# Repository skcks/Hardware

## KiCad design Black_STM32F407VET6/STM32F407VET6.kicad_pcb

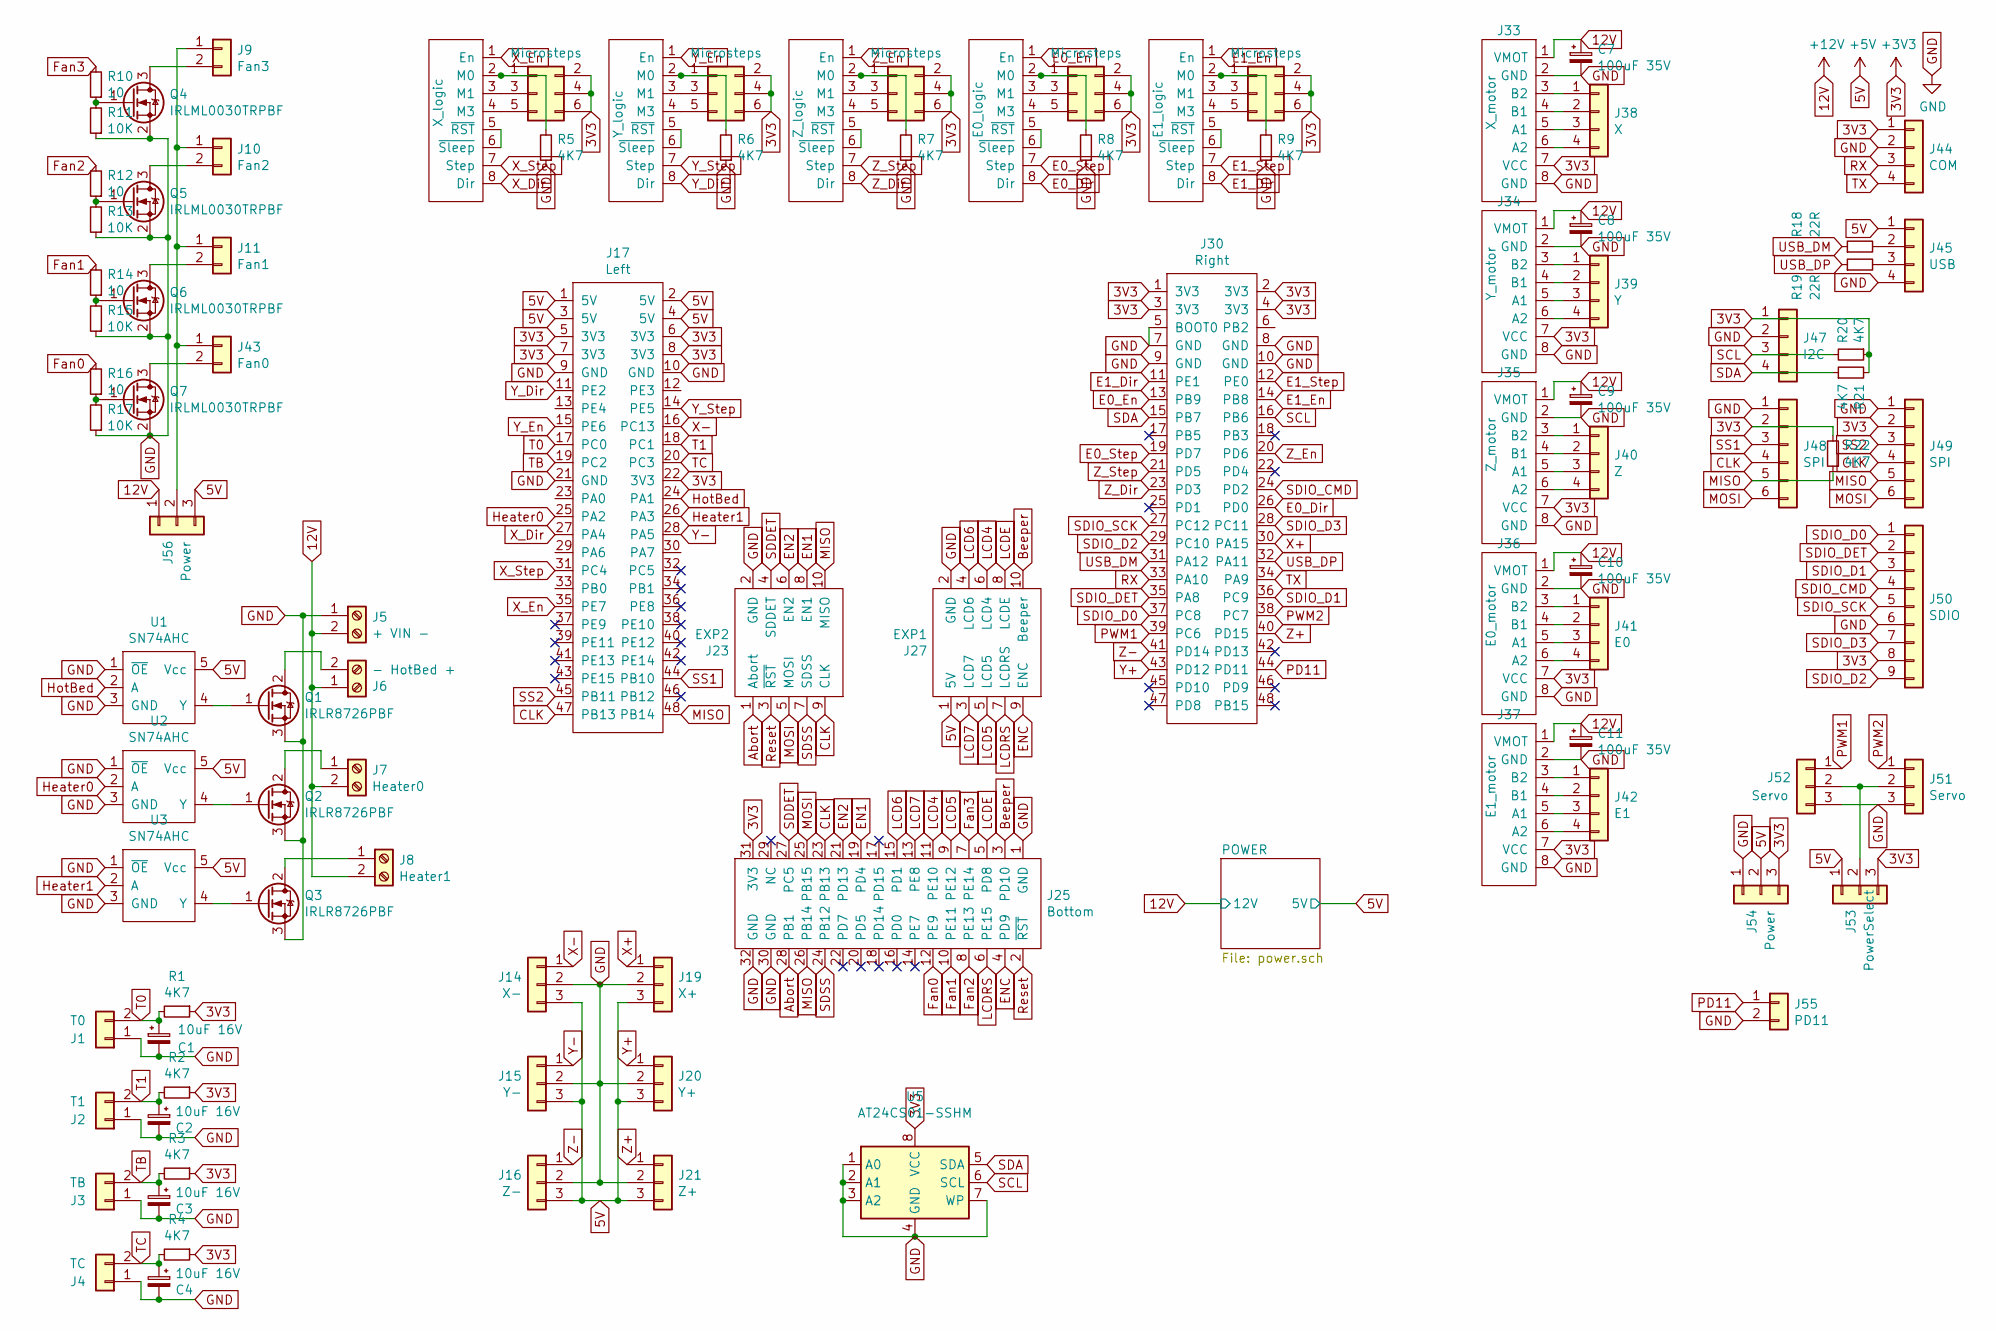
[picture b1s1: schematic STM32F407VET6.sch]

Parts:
C1, C2, C3, C4: 10uF 16V; CP_EIA-3216-10_Kemet-I
C7, C8, C9, C10, C11: 100uF 35V; CP_Elec_8x6.9
J1: T0; JST_XH_B02B-XH-A_1x02_P2.50mm_Vertical
J2: T1; JST_XH_B02B-XH-A_1x02_P2.50mm_Vertical
J3: TB; JST_XH_B02B-XH-A_1x02_P2.50mm_Vertical
J4: TC; JST_XH_B02B-XH-A_1x02_P2.50mm_Vertical
J5: + VIN -; TerminalBlock_MetzConnect_Type055_RT01502HDWU_1x02_P5.00mm_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
J6: - HotBed +; TerminalBlock_MetzConnect_Type055_RT01502HDWU_1x02_P5.00mm_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
J7: Heater0; TerminalBlock_MetzConnect_Type059_RT06302HBWC_1x02_P3.50mm_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
J8: Heater1; TerminalBlock_MetzConnect_Type059_RT06302HBWC_1x02_P3.50mm_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
J9: Fan3; JST_XH_B02B-XH-A_1x02_P2.50mm_Vertical
J10: Fan2; JST_XH_B02B-XH-A_1x02_P2.50mm_Vertical
J11: Fan1; JST_XH_B02B-XH-A_1x02_P2.50mm_Vertical
J12: X_logic; PinSocket_1x08_P2.54mm_Vertical
J13, J22, J26, J29, J32: Microsteps; PinHeader_2x03_P2.54mm_Vertical
J14: X-; JST_XH_B03B-XH-A_1x03_P2.50mm_Vertical
J15: Y-; JST_XH_B03B-XH-A_1x03_P2.50mm_Vertical
J16: Z-; JST_XH_B03B-XH-A_1x03_P2.50mm_Vertical
J17: Left; PinSocket_2x24_P2.54mm_Vertical
J18: Y_logic; PinSocket_1x08_P2.54mm_Vertical
J19: X+; JST_XH_B03B-XH-A_1x03_P2.50mm_Vertical
J20: Y+; JST_XH_B03B-XH-A_1x03_P2.50mm_Vertical
J21: Z+; JST_XH_B03B-XH-A_1x03_P2.50mm_Vertical
J23: EXP2; IDC-Header_2x05_P2.54mm_Vertical
J24: Z_logic; PinSocket_1x08_P2.54mm_Vertical
J25: Bottom; PinSocket_2x16_P2.54mm_Vertical
J27: EXP1; IDC-Header_2x05_P2.54mm_Vertical
J28: E0_logic; PinSocket_1x08_P2.54mm_Vertical
J30: Right; PinSocket_2x24_P2.54mm_Vertical
J31: E1_logic; PinSocket_1x08_P2.54mm_Vertical
J33: X_motor; PinSocket_1x08_P2.54mm_Vertical
J34: Y_motor; PinSocket_1x08_P2.54mm_Vertical
J35: Z_motor; PinSocket_1x08_P2.54mm_Vertical
J36: E0_motor; PinSocket_1x08_P2.54mm_Vertical
J37: E1_motor; PinSocket_1x08_P2.54mm_Vertical
J38: X; JST_XH_B04B-XH-A_1x04_P2.50mm_Vertical
J39: Y; JST_XH_B04B-XH-A_1x04_P2.50mm_Vertical
J40: Z; JST_XH_B04B-XH-A_1x04_P2.50mm_Vertical
J41: E0; JST_XH_B04B-XH-A_1x04_P2.50mm_Vertical
J42: E1; JST_XH_B04B-XH-A_1x04_P2.50mm_Vertical
J43: Fan0; JST_XH_B02B-XH-A_1x02_P2.50mm_Vertical
J44: COM; PinHeader_1x04_P2.54mm_Vertical
J45: USB; PinHeader_1x04_P2.54mm_Vertical
J47: I2C; PinHeader_1x04_P2.54mm_Vertical
J48, J49: SPI; PinHeader_1x06_P2.54mm_Vertical
J50: SDIO; JST_XH_B09B-XH-A_1x09_P2.50mm_Vertical
J51, J52: Servo; PinHeader_1x03_P2.54mm_Vertical
J53: PowerSelect; PinHeader_1x03_P2.54mm_Vertical
J54, J56: Power; PinHeader_1x03_P2.54mm_Vertical
J55: PD11; PinHeader_1x02_P2.54mm_Vertical
Q1, Q2, Q3: IRLR8726PBF; TO-252-2
Q4, Q5, Q6, Q7: IRLML0030TRPBF; SOT-23
R1, R2, R3, R4, R5, R6, R7, R8, R9, R20, R21, R22: 4K7; R_0603_1608Metric
R10, R12, R14, R16: 10; R_0603_1608Metric
R11, R13, R15, R17: 10K; R_0603_1608Metric
R18, R19: 22R; R_0603_1608Metric
U1, U2, U3: SN74AHC; SOT-23-5
U5: AT24CS01-SSHM; SOIC-8_3.9x4.9mm_P1.27mm

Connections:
3V3: J13.2, J13.4, J13.6, J17.5 (3V3), J17.6 (3V3), J17.7 (3V3), J17.8 (3V3), J17.22 (3V3), J22.2, J22.4, J22.6, J25.31 (3V3), J26.2, J26.4, J26.6, J29.2, J29.4, J29.6, J30.1 (3V3), J30.2 (3V3), J30.3 (3V3), J30.4 (3V3), J32.2, J32.4, J32.6, J33.7 (VCC), J34.7 (VCC), J35.7 (VCC), J36.7 (VCC), J37.7 (VCC), J44.1, J47.1, J48.2, J49.2, J50.8, J53.3, J54.3, R1.1, R2.1, R3.1, R4.1, R20.1, R21.2, R22.2, U5.8 (VCC)
5V: J14.3, J15.3, J16.3, J17.1 (5V), J17.2 (5V), J17.3 (5V), J17.4 (5V), J19.3, J20.3, J21.3, J27.1 (5V), J45.1, J53.1, J54.2, J56.3, U1.5 (Vcc), U2.5 (Vcc), U3.5 (Vcc); also elsewhere on the board
12V: C7.1, C8.1, C9.1, C10.1, C11.1, J5.2, J6.1, J7.2, J8.2, J33.1 (VMOT), J34.1 (VMOT), J35.1 (VMOT), J36.1 (VMOT), J37.1 (VMOT), J56.1; also elsewhere on the board
Abort: J23.1 (Abort), J25.28 (PB1)
Beeper: J25.3 (PD10), J27.10 (Beeper)
CLK: J17.47 (PB13), J23.9 (CLK), J25.23 (PB13), J48.4, J49.4
E0_Dir: J28.8 (Dir), J30.26 (PD0)
E0_En: J28.1 (En), J30.13 (PB9)
E0_Step: J28.7 (Step), J30.19 (PD7)
E1_Dir: J30.11 (PE1), J31.8 (Dir)
E1_En: J30.14 (PB8), J31.1 (En)
E1_Step: J30.12 (PE0), J31.7 (Step)
EN1: J23.8 (EN1), J25.19 (PD4)
EN2: J23.6 (EN2), J25.21 (PD13)
ENC: J25.4 (PD9), J27.9 (ENC)
Fan0: J25.12 (PE9), R16.2
Fan1: J25.10 (PE11), R14.2
Fan2: J25.8 (PE13), R12.2
Fan3: J25.7 (PE14), R10.2
GND: C1.2, C2.2, C3.2, C4.2, C7.2, C8.2, C9.2, C10.2, C11.2, J1.1, J2.1, J3.1, J4.1, J5.1, J14.2, J15.2, J16.2, J17.9 (GND), J17.10 (GND), J17.21 (GND), J19.2, J20.2, J21.2, J23.2 (GND), J25.1 (GND), J25.30 (GND), J25.32 (GND), J27.2 (GND), J30.5 (BOOT0), J30.7 (GND), J30.8 (GND), J30.9 (GND), J30.10 (GND), J33.2 (GND), J33.8 (GND), J34.2 (GND), J34.8 (GND), J35.2 (GND), J35.8 (GND), J36.2 (GND), J36.8 (GND), J37.2 (GND), J37.8 (GND), J44.2, J45.4, J47.2, J48.1, J49.1, J50.6, J51.3, J52.3, J54.1, J55.2, Q1.3 (S), Q2.3 (S), Q3.3 (S), Q4.2 (S), Q5.2 (S), Q6.2 (S), Q7.2 (S), R5.1, R6.1, R7.1, R8.1, R9.1, R11.1, R13.1, R15.1, R17.1, U1.1 (~OE), U1.3 (GND), U2.1 (~OE), U2.3 (GND), U3.1 (~OE), U3.3 (GND), U5.1 (A0), U5.2 (A1), U5.3 (A2), U5.4 (GND), U5.7 (WP); also elsewhere on the board
Heater0: J17.25 (PA2), U2.2 (A)
Heater1: J17.26 (PA3), U3.2 (A)
HotBed: J17.24 (PA1), U1.2 (A)
LCD4: J25.11 (PE10), J27.6 (LCD4)
LCD5: J25.9 (PE12), J27.5 (LCD5)
LCD6: J25.15 (PD1), J27.4 (LCD6)
LCD7: J25.13 (PE8), J27.3 (LCD7)
LCDE: J25.5 (PD8), J27.8 (LCDE)
LCDRS: J25.6 (PE15), J27.7 (LCDRS)
MISO: J17.48 (PB14), J23.10 (MISO), J25.26 (PB14), J48.5, J49.5, R22.1
MOSI: J23.5 (MOSI), J25.25 (PB15), J48.6, J49.6
unnamed: J6.2, Q1.2 (D)
unnamed: J7.1, Q2.2 (D)
unnamed: J8.1, Q3.2 (D)
unnamed: J9.2, Q4.3 (D)
unnamed: J9.1, J10.1, J11.1, J43.1, J56.2
unnamed: J10.2, Q5.3 (D)
unnamed: J11.2, Q6.3 (D)
unnamed: J12.2 (M0), J13.1, R5.2
unnamed: J12.3 (M1), J13.3
unnamed: J12.4 (M3), J13.5
unnamed: J12.5 (~RST), J12.6 (~Sleep)
unnamed: J18.2 (M0), J22.1, R6.2
unnamed: J18.3 (M1), J22.3
unnamed: J18.4 (M3), J22.5
unnamed: J18.5 (~RST), J18.6 (~Sleep)
unnamed: J24.2 (M0), J26.1, R7.2
unnamed: J24.3 (M1), J26.3
unnamed: J24.4 (M3), J26.5
unnamed: J24.5 (~RST), J24.6 (~Sleep)
unnamed: J28.2 (M0), J29.1, R8.2
unnamed: J28.3 (M1), J29.3
unnamed: J28.4 (M3), J29.5
unnamed: J28.5 (~RST), J28.6 (~Sleep)
unnamed: J31.2 (M0), J32.1, R9.2
unnamed: J31.3 (M1), J32.3
unnamed: J31.4 (M3), J32.5
unnamed: J31.5 (~RST), J31.6 (~Sleep)
unnamed: J33.3 (B2), J38.1
unnamed: J33.4 (B1), J38.2
unnamed: J33.5 (A1), J38.3
unnamed: J33.6 (A2), J38.4
unnamed: J34.3 (B2), J39.1
unnamed: J34.4 (B1), J39.2
unnamed: J34.5 (A1), J39.3
unnamed: J34.6 (A2), J39.4
unnamed: J35.3 (B2), J40.1
unnamed: J35.4 (B1), J40.2
unnamed: J35.5 (A1), J40.3
unnamed: J35.6 (A2), J40.4
unnamed: J36.3 (B2), J41.1
unnamed: J36.4 (B1), J41.2
unnamed: J36.5 (A1), J41.3
unnamed: J36.6 (A2), J41.4
unnamed: J37.3 (B2), J42.1
unnamed: J37.4 (B1), J42.2
unnamed: J37.5 (A1), J42.3
unnamed: J37.6 (A2), J42.4
unnamed: J43.2, Q7.3 (D)
unnamed: J45.2, R18.2
unnamed: J45.3, R19.2
unnamed: J51.2, J52.2, J53.2
unnamed: Q1.1 (G), U1.4 (Y)
unnamed: Q2.1 (G), U2.4 (Y)
unnamed: Q3.1 (G), U3.4 (Y)
unnamed: Q4.1 (G), R10.1, R11.2
unnamed: Q5.1 (G), R12.1, R13.2
unnamed: Q6.1 (G), R14.1, R15.2
unnamed: Q7.1 (G), R16.1, R17.2
PD11: J30.44 (PD11), J55.1
PWM1: J30.39 (PC6), J52.1
PWM2: J30.38 (PC7), J51.1
RX: J30.33 (PA10), J44.3
Reset: J23.3 (~RST), J25.2 (~RST)
SCL: J30.16 (PB6), J47.3, R20.2, U5.6 (SCL)
SDA: J30.15 (PB7), J47.4, R21.1, U5.5 (SDA)
SDDET: J23.4 (SDDET), J25.27 (PC5)
SDIO_CMD: J30.24 (PD2), J50.4
SDIO_D0: J30.37 (PC8), J50.1
SDIO_D1: J30.36 (PC9), J50.3
SDIO_D2: J30.29 (PC10), J50.9
SDIO_D3: J30.28 (PC11), J50.7
SDIO_DET: J30.35 (PA8), J50.2
SDIO_SCK: J30.27 (PC12), J50.5
SDSS: J23.7 (SDSS), J25.24 (PB12)
SS1: J17.44 (PB10), J48.3
SS2: J17.45 (PB11), J49.3
T0: C1.1, J1.2, J17.17 (PC0), R1.2
T1: C2.1, J2.2, J17.18 (PC1), R2.2
TB: C3.1, J3.2, J17.19 (PC2), R3.2
TC: C4.1, J4.2, J17.20 (PC3), R4.2
TX: J30.34 (PA9), J44.4
USB_DM: J30.31 (PA12), R18.1
USB_DP: J30.32 (PA11), R19.1
X+: J19.1, J30.30 (PA15)
X-: J14.1, J17.16 (PC13)
X_Dir: J12.8 (Dir), J17.27 (PA4)
X_En: J12.1 (En), J17.35 (PE7)
X_Step: J12.7 (Step), J17.31 (PC4)
Y+: J20.1, J30.43 (PD12)
Y-: J15.1, J17.28 (PA5)
Y_Dir: J17.11 (PE2), J18.8 (Dir)
Y_En: J17.15 (PE6), J18.1 (En)
Y_Step: J17.14 (PE5), J18.7 (Step)
Z+: J21.1, J30.40 (PD15)
Z-: J16.1, J30.41 (PD14)
Z_Dir: J24.8 (Dir), J30.23 (PD3)
Z_En: J24.1 (En), J30.20 (PD6)
Z_Step: J24.7 (Step), J30.21 (PD5)

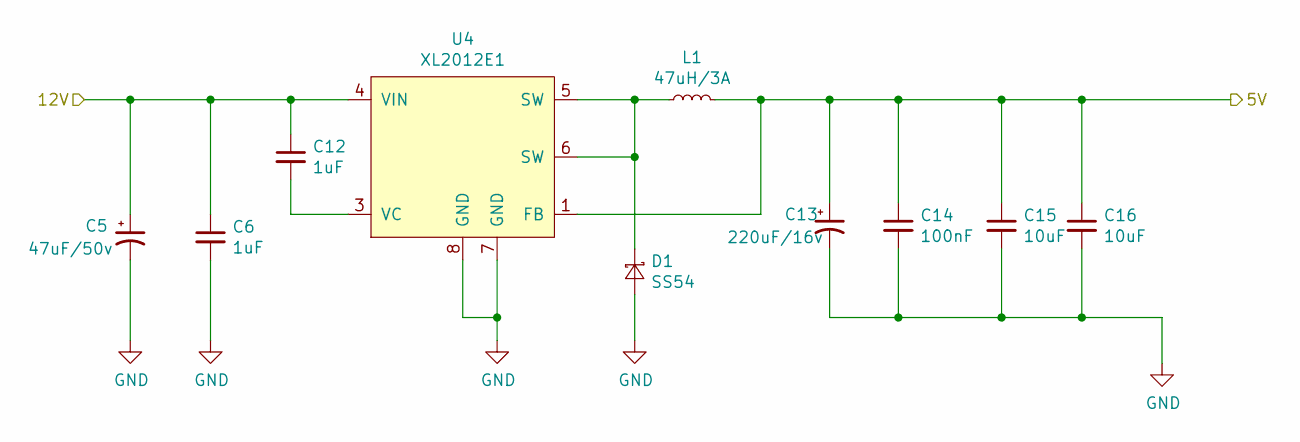
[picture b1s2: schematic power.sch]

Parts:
C5: 47uF/50v; CP_Elec_6.3x7.7
C6, C12: 1uF; C_0805_2012Metric
C13: 220uF/16v; CP_Elec_8x10
C14: 100nF; C_0805_2012Metric
C15, C16: 10uF; C_0805_2012Metric
D1: SS54; D_SMA
L1: 47uH/3A; L_7.3x7.3_H4.5
U4: XL2012E1; SOIC-8_3.9x4.9mm_P1.27mm

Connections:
5V: C13.1, C14.1, C15.1, C16.1, L1.2, U4.1 (FB); also elsewhere on the board
12V: C5.1, C6.1, C12.1, U4.4 (VIN); also elsewhere on the board
GND: C5.2, C6.2, C13.2, C14.2, C15.2, C16.2, D1.2 (A), U4.7 (GND), U4.8 (GND); also elsewhere on the board
unnamed: C12.2, U4.3 (VC)
unnamed: D1.1 (K), L1.1, U4.5 (SW), U4.6 (SW)

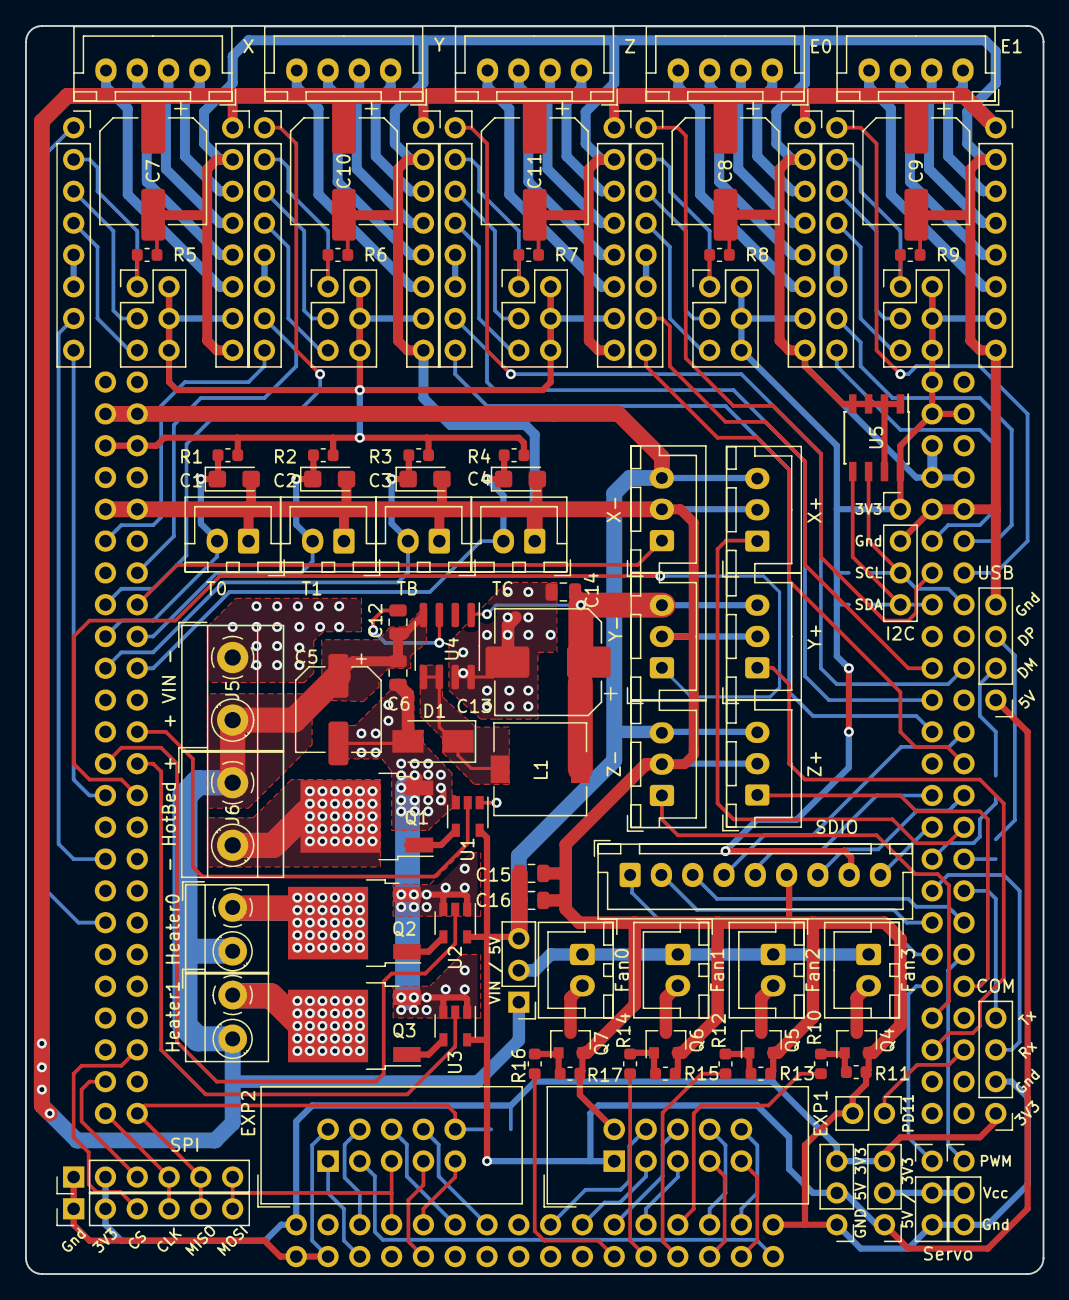
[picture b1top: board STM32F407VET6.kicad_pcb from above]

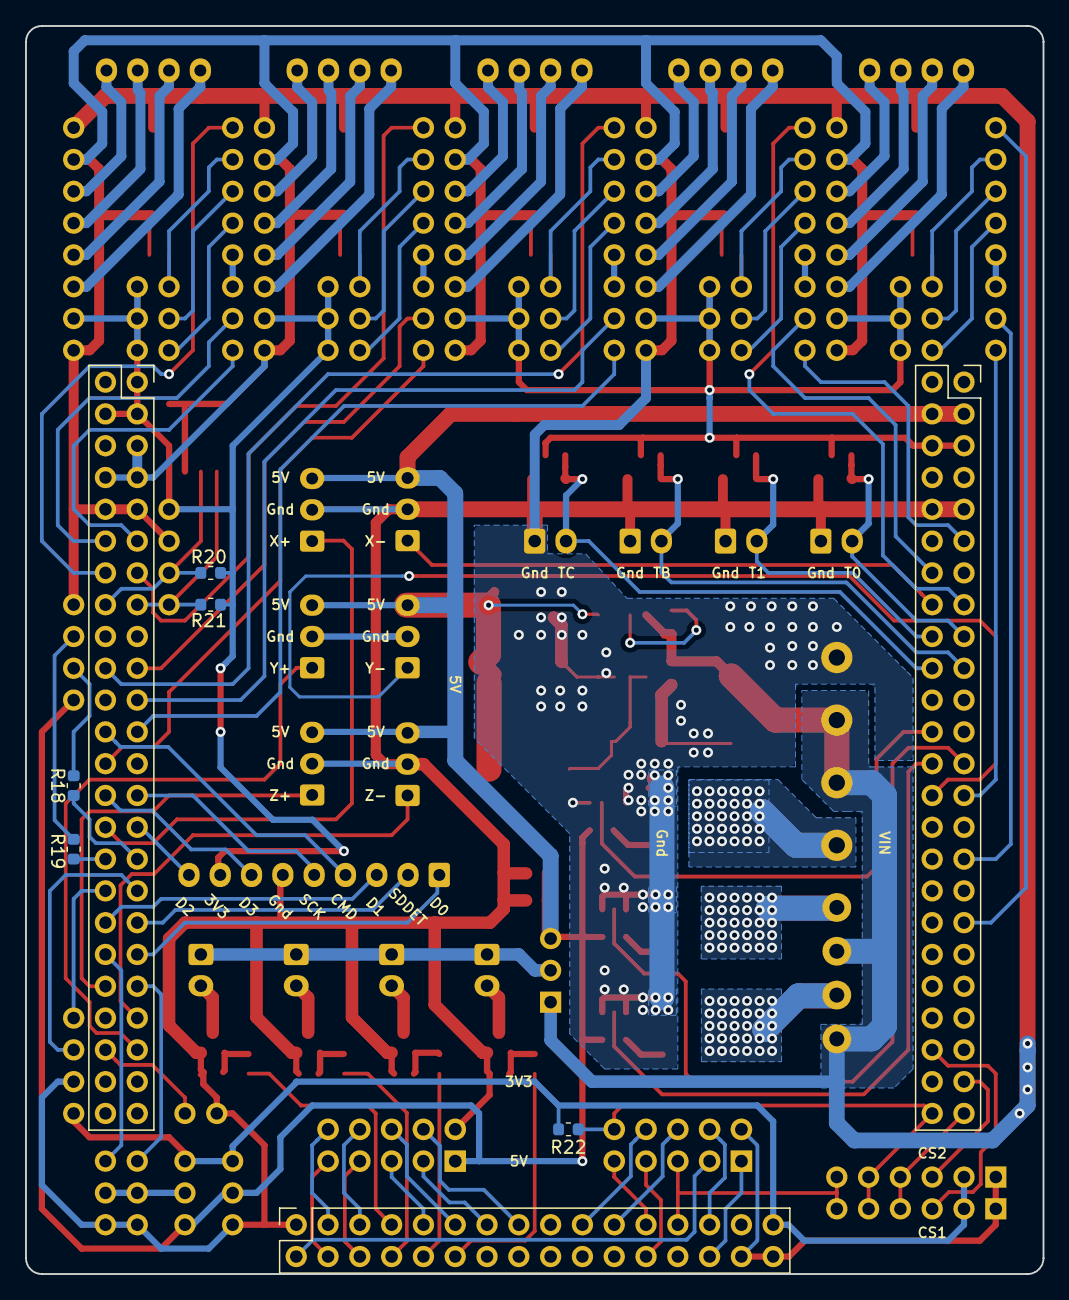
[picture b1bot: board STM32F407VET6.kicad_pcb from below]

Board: 2 copper layers, 81.3 x 99.7 mm, 107 parts (8 on the bottom side), 131 nets.

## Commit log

2019-06-11 change dcdc chip
2019-06-11 optimize for current
2019-06-11 optimize tracks
2019-06-13 change large cap for dcdc output
